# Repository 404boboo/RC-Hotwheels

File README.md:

# RC-Hotwheels
This project is a remote controlled Hotwheels. Here you can find the Ki-cad design files and STM32 project

This repository contains all the files and documentation for our DIY remote-controlled Hot Wheels car. We designed our own custom PCB using KiCad, featuring a NRF24L01 transceiver(We only used it as a receiver for now) for wireless communication, an H-bridge BD6211F-E2 to control a DC motor for propulsion, a 600mAh LiPo battery for power, and a linear servo motor for precise steering control.
## Folder Structure

- `Kicad Files`: Contains the schematic and gerber files for the PCB design.
  - `Libs`: Libraries for the components used in the KiCad.
- `Stm32F070F6P6TR`: STM32Cube project folder.
## Bill of Materials (BOM)

Check out our [Bill of Materials Spreadsheet](https://1drv.ms/x/s!AkUVCTQvexeIhbBXzQdKwvWQZ13EOg?e=rf4EnU) for a detailed list of components used in this project.
## Installation and Setup

### PCB (KiCad Files)

1. Download the KiCad software from [kicad.org](https://www.kicad.org/).
2. Open the KiCad project files in the `Kicad Files` folder.
3. Generate the gerber files for manufacturing.

### STM32Cube Project

-- TODO

### Hardware

1. Assemble the custom PCB according to the provided schematic.
2. Connect the NRF24L01 transceiver
-- To be updated..

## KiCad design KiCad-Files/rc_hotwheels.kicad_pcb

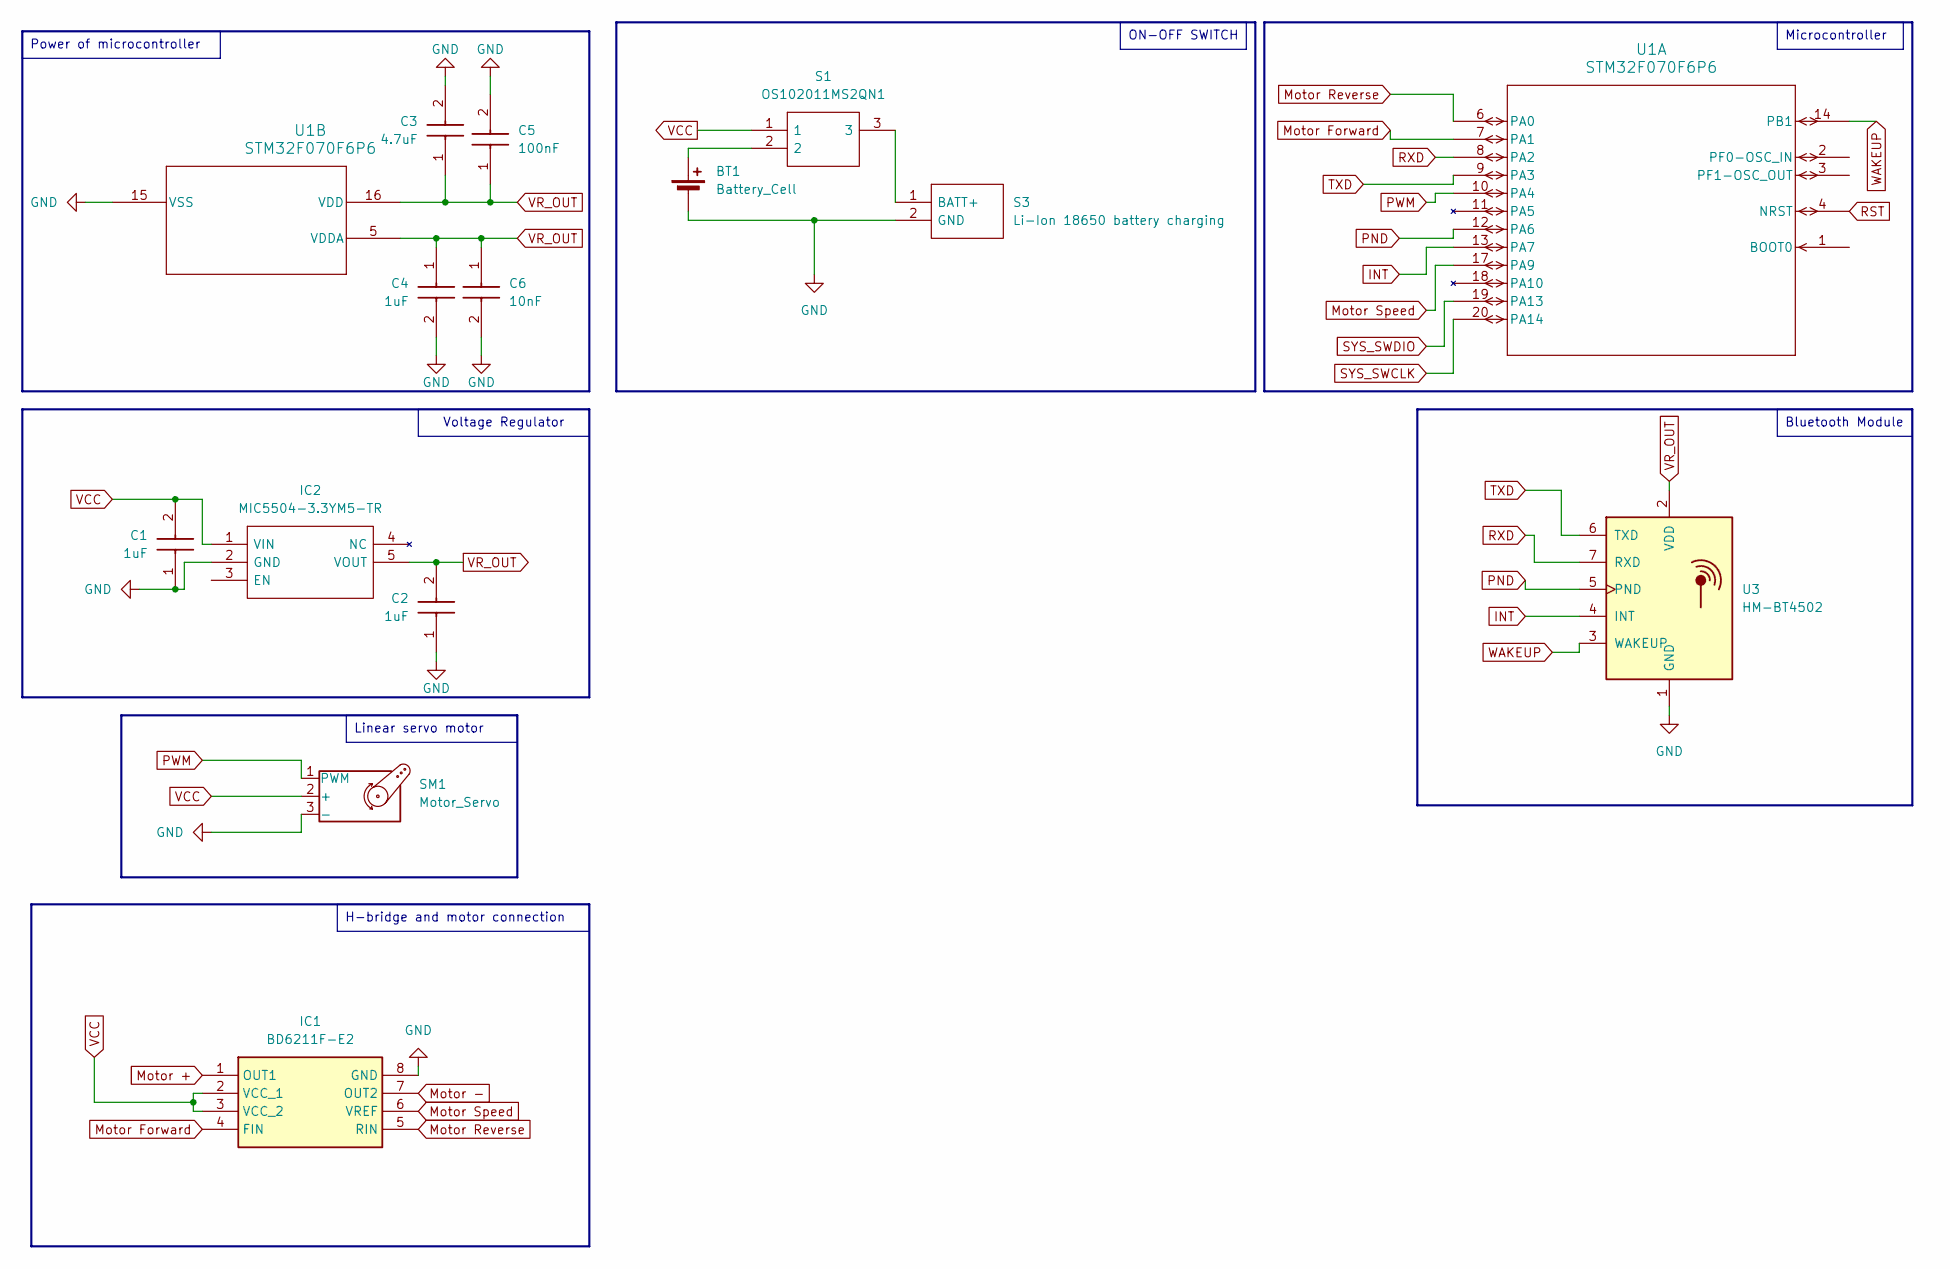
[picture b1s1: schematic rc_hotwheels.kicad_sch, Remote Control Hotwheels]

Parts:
BT1: Battery_Cell; Battery_Pads
C1, C2, C4: 1uF; CAPC2012X135N; Manufacturer_Part_Number 885012209003
C3: 4.7uF; CAPC2012X135N; Manufacturer_Part_Number 885012209004
C5: 100nF; CAPC2012X135N; Manufacturer_Part_Number 885012209041
C6: 10nF; CAPC2012X135N; Manufacturer_Part_Number 885012209035
IC1: BD6211F-E2; SOIC127P620X171-8N; Manufacturer_Part_Number BD6211F-E2
IC2: MIC5504-3.3YM5-TR; SOT95P280X145-5N; Manufacturer_Part_Number MIC5504-3.3YM5-TR; Mouser Part Number 998-MIC5504-3.3YM5TR
S1: OS102011MS2QN1; OS102011MA1QN1; Manufacturer_Part_Number OS102011MS2QN1
S3: Li-Ion 18650 battery charging; Battery_Pads; Manufacturer_Part_Number OS102011MS2QN1
SM1: Motor_Servo; Servo_Motor
U1: STM32F070F6P6; SOP65P640X120-20N
U3: HM-BT4502; nRF24L01_Breakout

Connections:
GND: BT1.2 (-), C1.1, C2.1, C3.2, C4.2, C5.2, C6.2, IC1.8 (GND), IC2.2 (GND), S3.2 (GND), SM1.3 (-), U1.15 (VSS), U3.1 (GND), U3.8; also elsewhere on the board
INT: U1.13 (PA7), U3.4 (INT)
Motor +: IC1.1 (OUT1); also elsewhere on the board
Motor -: IC1.7 (OUT2); also elsewhere on the board
Motor Forward: IC1.4 (FIN), U1.7 (PA1)
Motor Reverse: IC1.5 (RIN), U1.6 (PA0)
Motor Speed: IC1.6 (VREF), U1.17 (PA9)
unnamed: BT1.1 (+), S1.2
unnamed: S1.3, S3.1 (BATT+)
PND: U1.12 (PA6), U3.5 (PND)
PWM: SM1.1 (PWM), U1.10 (PA4)
RST: U1.4 (NRST); also elsewhere on the board
RXD: U1.8 (PA2), U3.7 (RXD)
SYS_SWCLK: U1.20 (PA14); also elsewhere on the board
SYS_SWDIO: U1.19 (PA13); also elsewhere on the board
TXD: U1.9 (PA3), U3.6 (TXD)
VCC: C1.2, IC1.2 (VCC_1), IC1.3 (VCC_2), IC2.1 (VIN), S1.1, SM1.2 (+)
VR_OUT: C2.2, C3.1, C4.1, C5.1, C6.1, IC2.5 (VOUT), U1.5 (VDDA), U1.16 (VDD), U3.2 (VDD); also elsewhere on the board
WAKEUP: U1.14 (PB1), U3.3 (WAKEUP)

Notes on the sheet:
Bluetooth Module
ON-OFF SWITCH
Linear servo motor
Voltage Regulator
Power of microcontroller
H-bridge and motor connection
Microcontroller

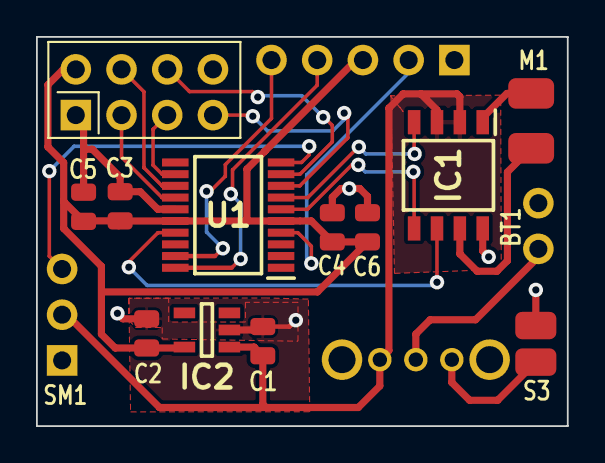
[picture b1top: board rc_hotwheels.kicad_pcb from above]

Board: 2 copper layers, 29.5 x 21.6 mm, 16 parts (1 on the bottom side), 19 nets.

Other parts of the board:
M1: Motor_Connection
ST: ST_Link

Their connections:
GND: ST.1; also elsewhere on the board
Motor +: M1.2; also elsewhere on the board
Motor -: M1.1; also elsewhere on the board
RST: ST.2; also elsewhere on the board
SYS_SWCLK: ST.4; also elsewhere on the board
SYS_SWDIO: ST.5; also elsewhere on the board
VR_OUT: ST.3; also elsewhere on the board

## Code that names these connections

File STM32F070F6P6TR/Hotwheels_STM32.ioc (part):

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Mcu.Name=STM32F070F6Px
Mcu.Package=TSSOP20
Mcu.UserName=STM32F070F6Px
PA0.GPIOParameters=GPIO_Label
PA0.GPIO_Label=MotorReverse
PA0.Signal=GPIO_Output
PA1.GPIOParameters=GPIO_Label
PA1.GPIO_Label=MotorForward
PA1.Signal=GPIO_Output
PA13.Mode=Serial_Wire
PA13.Signal=SYS_SWDIO
PA14.Mode=Serial_Wire
PA14.Signal=SYS_SWCLK
PA2.Mode=Asynchronous
PA2.Signal=USART2_TX
PA3.Mode=Asynchronous
PA3.Signal=USART2_RX
PA4.GPIOParameters=GPIO_Label
PA4.GPIO_Label=Servo Control
PA4.Signal=S_TIM14_CH1
PA6.GPIOParameters=GPIO_Label
PA6.GPIO_Label=PDN
PA6.Signal=GPIO_Output
PA7.GPIOParameters=GPIO_Label
PA7.GPIO_Label=INT
PA7.Signal=GPIO_Input
PA9.GPIOParameters=GPIO_Label
PA9.GPIO_Label=Motor Speed
PA9.Signal=S_TIM1_CH2
PB1.GPIOParameters=GPIO_Label
PB1.GPIO_Label=WAKEUP
PB1.Signal=GPIO_Output
PF0-OSC_IN.Mode=HSE-External-Oscillator
PF0-OSC_IN.Signal=RCC_OSC_IN
PF1-OSC_OUT.Mode=HSE-External-Oscillator
PF1-OSC_OUT.Signal=RCC_OSC_OUT
RCC.SYSCLKFreq_VALUE=48000000
RCC.SYSCLKSource=RCC_SYSCLKSOURCE_PLLCLK
board=custom

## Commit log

2023-11-23 Starting point
2023-11-28 Improved github project files structure.
2023-11-28 Added H-Bridge symbol and connection.
2023-11-28 ignore file added
2023-11-29 Added receiver symbol and connections
2023-11-29 Creation of STM32 project
2023-11-29 nR4F24 configurations, pinout, and library added
2023-11-29 Updated the nRF24L01 connection to the MCU.
2023-11-29 Servo motor
2023-11-29 Added name tags to components
2023-11-29 visual update
2023-11-29 Added the PMW pin for servo on STM32
2023-11-29 changed the servo pin to p4
2023-11-30 Enabled Debug Serial Wire for the MCU
2023-12-04 Motor connections and configurations updated(Forward, Reverse, Speed)
2023-12-04 Servo motor connection and configurations updated.
2023-12-11 Added Voltage Regulator symbol, connections and improved STM pinout user label
2023-12-13 Added capacitors to the MCU and Voltage Regulator
2023-12-22 Capacitors footprints added
    Capacitor_THT:C_Rect_L4.6mm_W2.0mm_P2.50mm_MKS02_FKP02
2023-12-22 Servo motor connection
    Deleted unused component - servo motor, instead used mounting holes
2023-12-22 Mounting holes footprints added
2023-12-23 Added more capacitors for power supply of MCU
2023-12-23 Added all library files for KiCad
2023-12-23 Footprint and Symbol libraries imported
2023-12-25 Updated MCU footprint
2023-12-28 Created PCB Design
    - Placed Components at the right place. Connected Voltage Regulator chip to MCU.
    - Changed Capacitors Footprint and Symbol.
2023-12-28 PCB Design
    Connecting the Transceiver
2023-12-29 PCB updated
    Mostly connections for H-Bride to motor and Servo Motor.
2023-12-30 Fixed all schematic errors.
2023-12-30 Updated and imported 3D models for all components
2023-12-30 Created and imported footprints for Battery and Servo Motor connection
2023-12-31 PCB V2.0
2024-01-01 PCB V2.1
    - Reduced the height size of the PCB(moved components closer to each other).
    - Connected all GNDs to each other.
2024-01-10 Updated all power traces
2024-01-10 Updated Capcitors libs
2024-01-11 PCB V2.2
    -Updated Capacitors footprint
    -Added reset pin for the MCU.
    -PCB design improved
2024-01-14 Fixed GNDS not connected.
2024-01-14 PCB Update
    Fixed all errors & warnings
    Made the thermal reliefs bigger
2024-01-14 Merge branch 'master' of https://github.com/404boboo/RC-Hotwheels
    Small changes in tracing
2024-01-14 Files update
    Schematic PDF added
2024-01-14 Files update
    Gerber and drill files added
2024-01-14 Files update
    Bill of materials added
2024-09-19 Changed Radio Receiver to Bluetooth Module
